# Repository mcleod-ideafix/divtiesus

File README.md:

# DivTIESUS
DivTIESUS is a SD/MMC card interface for the ZX Spectrum. First designed by Mario Pratto as DivMMC, DivTIESUS is an independent design, compatible with the I/O ports and mapper used both in DivIDE and DivMMC, but adding more features.

There is a larger version of DivTIESUS, nicknamed "Pijus Magnificus" edition. This one is the "Tiesus del tó" version, which I have released for the community, so anyone can build his/her own interface.

# Features
- DivMMC compatible interface with 8 KiB of EEPROM and 128 KiB of RAM. Standard utils for EEPROM flashing, as provided by the ESXDOS team, are compatible with DivTIESUS.
- Model autodetection. This means you don't need to put a jumper, or flip a switch to change from using it with a Spectrum 48K and a +3.
- Tested with ZX Spectrum 48K issue 1, 2, 3, 3B, 4A, 4B and 6A. NEC and Hitachi ROM chips. Also tested on Inves Spectrum, Spectrum 128K (both english and spanish versions), +2 grey, +2A, +2B and +3. Also tested on Harlequin 48K. Compatible with TK90X also.
- It uses its own fast clock (25 MHz). It does not need the CPU clock at all.
- Rear expansion port continuation, allowing the user to plug another device. Note that ROMCS and other signals are not filtered.
- NMI button to call file browser in ESXDOS, and handy RESET button. The RESET button is placed so that it won't be accidentally pressed while operating the interface.
- Standard SD card slot (accepts both big SD cards and microSD cards (with adapter).
- A single switch is used to indicate DivTIESUS that the EEPROM can be flashed (JP2 equivalent) and the automapping feature is disabled.
- Visual feedback for SD activity (blue led) and update EEPROM mode (red led).
- ESXDOS shadowing does not collide with all-RAM feature in +2A/B/3 machines. If the system is in all-RAM mode, ESXDOS ROM mapping is disabled.
- Soft +3E feature: DivTIESUS is able to load +3E ROM images from the SD card, install them as the system ROM (using its own RAM), and make them available to the computer, while disabling the automapping feature (needed for ESXDOS but not for +3eDOS). This, effectively, allows the user to operate his/her +2A/B/3 machine as a +2e/3e one, all without having to open the case and exchange ROMs. A new dot command, ".go3e" makes this possible. Such command only works with DivTIESUS.
- Soft ROM feature: the soft +3E feature can also be used to load any 16K, 32K or 64K ROM and make the computer to boot with that ROM (the dot command currently supports only 16K ROMs). This means that ROM images for some util/games available for the Spectrum can be run in their original form. No need to have a +2A/B/3 machine to use them.

# Pictures

# Schematic, board and layout (top and flipped bottom side)

# Build
- First, you need the DivTIESUS PCB. You can order it from JLCPCB using the files in "gerber" directory. They are already tailored for JLCPCB PCB process.
- Second: get the component list. Following is the BOM, with Mouser references to get parts from them, but most of the components are rather standard so you can get it from severla other distributors. Many of them can also be obtained from Aliexpress.

## Bill of materials
|Qty|Value|PCB part|Mouser ref.|
| ------------ | ------------ | ------------ | ------------ |
|2|WS-TATU-TH 431256058726|NMI, RESET|710-431256058726|
|1|SDCARD SLOT|SDCARD|523-GMC020080HR|
|2|1K|R1, R5|603-RC0603FR-131KL|
|5|10K|R2, R4, R6, R7, R8|603-RC0603FR-1310KL|
|3|10uF|C1, C2, C13|581-0805YC106KAT2A|
|1|22K|R3|603-RC0603FR-1322KL|
|1|25 MHz 3225|Q1|520-3225Q-33-240-BST|
|1|28C64ASO|IC2|556-AT28C64B15SU|
|10|100nF|C3, C4, C5, C6, C7, C8, C9, C10, C11, C12|581-0603YC104J4T4A|
|1|CONECTOR_BUS_TRASERO|U$1|571-5530843-6|
|1|EPM240T100C4|IC3|989-EPM240T100C4|
|1|IS65C1024ALSO32|IC4|727-CY62128ELL45SXIT|
|1|JTAG|JTAG|517-N2510-6002RB|
|1|LED0805-BLUE|SD ACTIVITY|710-150080BS75000|
|1|LED0805-RED|FIRMWARE UPDATE ENABLED|710-150080RS75000|
|1|LM1117-3.3|IC1|511-LD1117S33|
|1|SWITCH_SMD_6PIN|JUMPER_E|4000030382277 (Aliexpress)|

- The oscillator does not need to be 25 MHz. It can be about any value between 14 and 30 MHz (it may even work with values outside these limits -not tested-)
- It is very advisable to use a stencil and solder paste for the soldering process. You don't really need a reflow oven, as parts can be soldered using hot air. There are plenty of Youtube videos covering the matter.
- Start placing passives (resistors, capacitors, going from right to left. Leave the SRAM, EEPROM, SD socket and CPLD for the end (in this order). Don't place thru-hole components yet.
- Reflow the top side using an oven, hot plate or hot air. For two pad parts you can even apply the solder tip a few seconds on each pad to allow reflowing it, while keeping the part in place with a pair of tweezers. Same method can be used with SOT-223 parts (the 3.3V regulator), the SD card slot and the SMD switch.
- Turn the board and put-place-solder the two leds. Be aware of polarity with them. Also be aware that these components are very delicate and won't hold much heat, so try to not to apply too much heat and for too much time. You can see in the PCB that (K)athode and (A)node are marked. If you don't like red and blue, use whichever colours you like (or have available).

## First electrical testing
- Check that there is no shortcircuits at the 5V and 3.3V power rails.
- Check that there is no shorts between adjacent pads at the CPLD chip. You may need a magnifying glass to do that. Shorts between adjacent pins at the SRAM or CPLD are easier to notice (I hope).
- To fix any shorts, paste flux is your very best friend. Use it wisely. To me, AMTECH NC-559 solder flux is the best thing to have around (be aware of imitations in Aliexpress!)

After all this first checks, proceed to build and solder the ZX Spectrum bus connector:

## ZX Spectrum bus connector
- Take the 2x28 pin edge connector and cut about 1-2mm on each side to leave the ends opened, as in the last picture of this section.
- With a pair of tweezers, pull and extract the two metal contacts that are positioned at 5th place, where the index tab will be.

- Now take a small piece you can get from a PCB, 1.5mm thick and 7mm tall. This will be the index tab.

- Place the piece in the index hole. Sand it if it's too tall for the hole.

- Using a pair of pliers, push it in place. If it's too small for the hole, use some glue to keep it from coming loose.

Now the edge connector is ready to work as a ZX Spectrum rear bus connector!                                                      

# FAQ (in progress)
***Is this the same version as you have already on sale?***
Almost! This version is the basic version, which is also the cheapest one I've made. Although it's the "basic" version, it has plenty of features, not present in any other DivMMC-like interface, atm.

***Can I take this, build or have someone else build some units, sell them and make some profit?***
I'm ok with that. I only ask you two things: do not remove my copyright noptice from the silk screen and any other document present in this repository, and if you make changes, additions, or otherwise improve the board, make those changes public and available for others as well.

***Can I adapt the Verilog code for a Xilinx part, like XC95144XL?***
Yes, but take into account that XC95 CPLDs doesn't have programmmable pull-ups, so you might need to add some 10K resistors to the board.

***Can I use 512K SRAM chips instead of 128K? Will the board recognize and use it at full capacity?***
Yes to both questions.

***I can see a "divmmc_mcleod_nom1.v" file with a version of the DivMMC module that isn't being used. What is that for?***
Glad you asked! It's an experimental DivMMC module that **DOESN'T NEED THE M1 SIGNAL FROM THE Z80**. It's experimental in the way that it works most of the time, but sometimes, not. If you program the CPLD with this version, it will use the RFSH signal instead of M1 to map and unmap the EEPROM, and a slighly sofisticated method to find out if it is in a M1 cycle, or memory read cycle, to inmediately map the EEPROM for TRDOS traps. More on this later.

***What "tiesus-del-tó" means?***
It means "really really broke".

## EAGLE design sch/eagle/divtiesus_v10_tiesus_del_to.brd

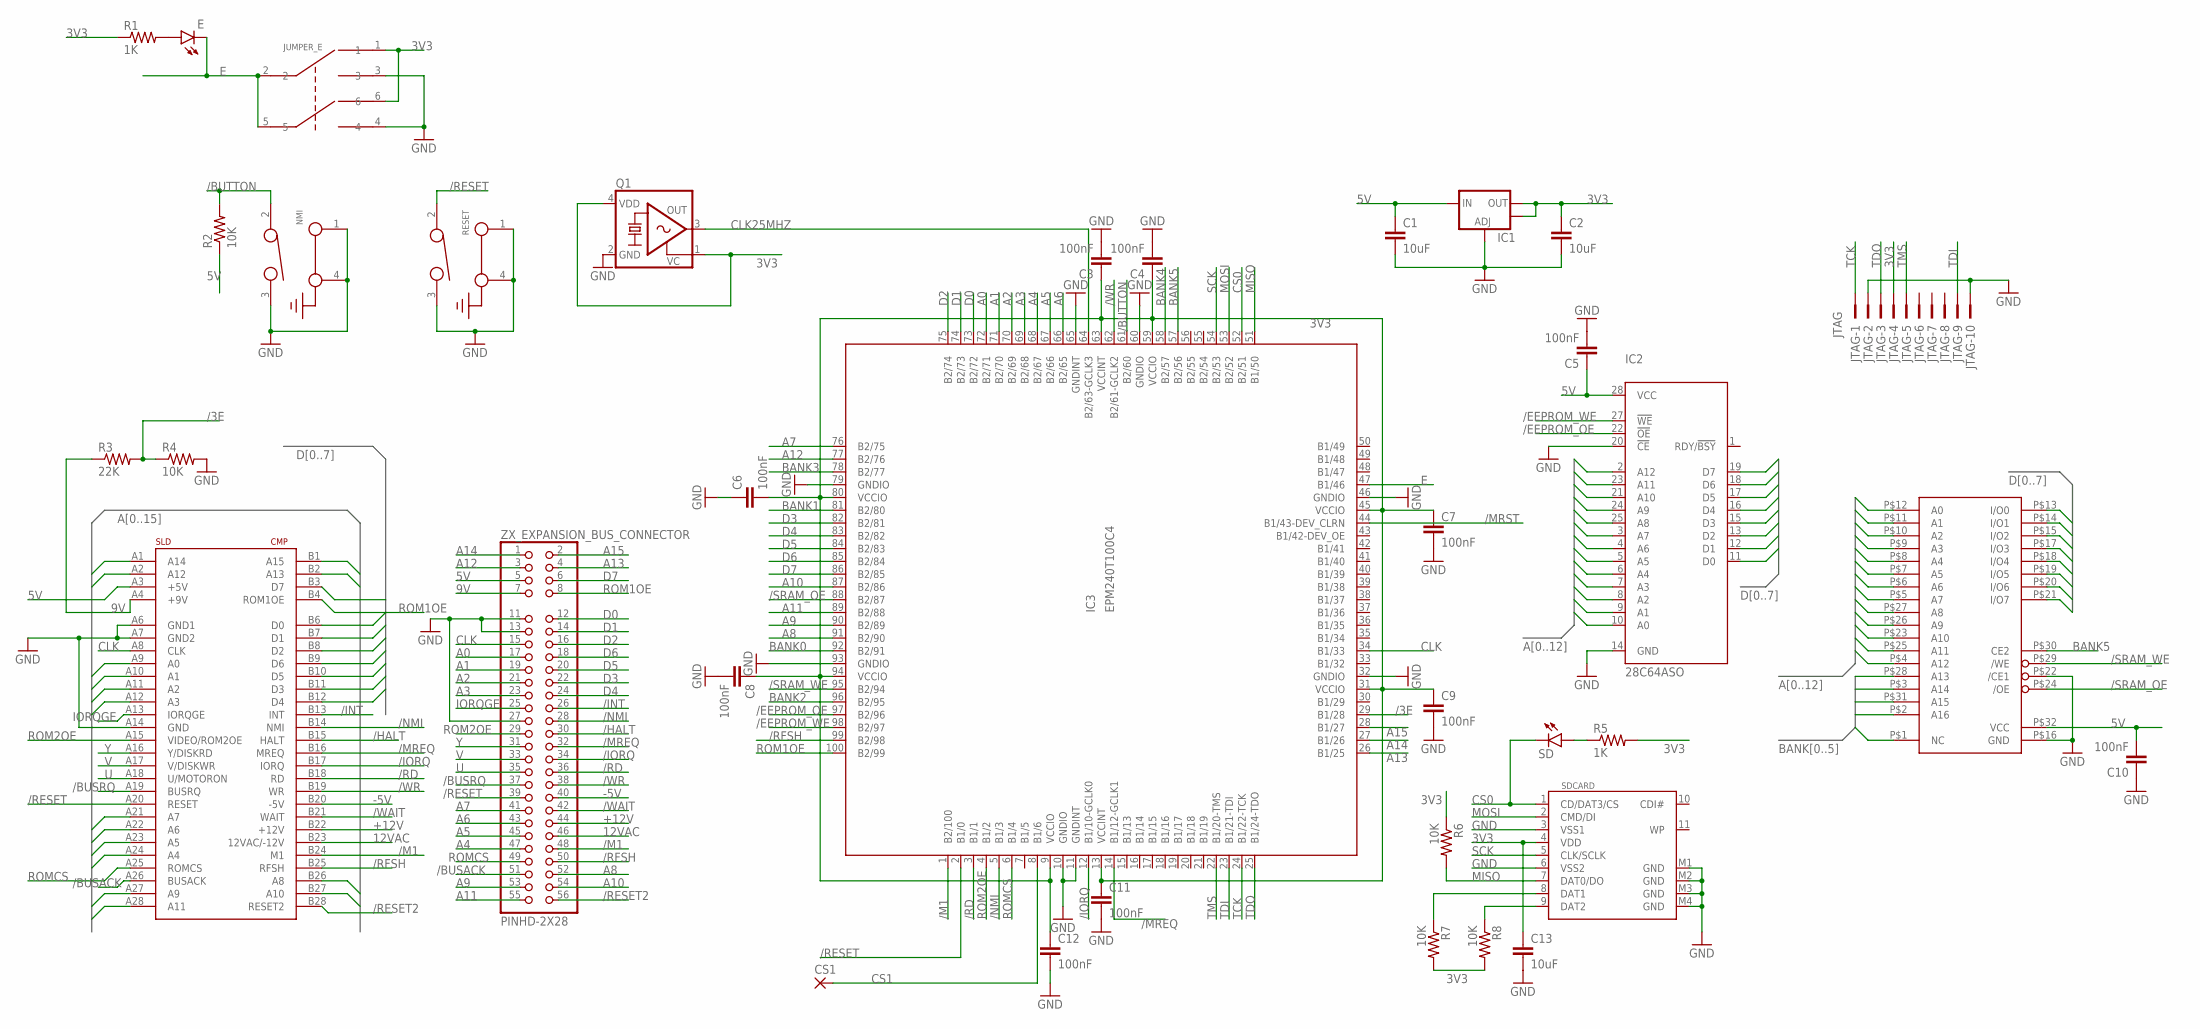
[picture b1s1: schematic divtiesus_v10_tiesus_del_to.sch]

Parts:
C1, C2, C13: 10uF; C0805
C3, C4, C5, C6, C7, C8, C9, C10, C11, C12: 100nF; C0603K
CS1: SMD2; SMD1,27-2,54
E: LEDCHIPLED_0805; CHIPLED_0805
IC1: V_REG_LM1117SOT223; SOT223
IC2: 28C64ASO; SO28W
IC3: EPM240T100C4; TQFP100
IC4: IS65C1024ALSO32; SO32-545MIL
JTAG: JTAG; PAK100/2500-10
JUMPER_E: SWITCH_SMD_6PIN; SMD-6PIN
NMI: 431256083716
Q1: KXO-VCTCXO-SINE-84; 3.2X2.5_KXO-84-VCTCXO
R1, R5: 1K; R0603
R2, R4, R6, R7, R8: 10K; R0603
R3: 22K; R0603
RESET: 431256083716
SD: LEDCHIPLED_0805; CHIPLED_0805
SDCARD: SDCARD; SDCMF-10915W010
U$1: CONECTOR_BUS_TRASERO; CONECTOR_SIMPLE_CARA
ZX_EXPANSION_BUS_CONNECTOR: PINHD-2X28; 2X28

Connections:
3V3: C2.1, C3.1, C4.1, C6.2, C7.1, C8.1, C9.1, C11.1, C12.1, C13.1, IC1.2 (OUT), IC1.4 (OUT), IC3.9 (VCCIO), IC3.13 (VCCINT), IC3.31 (VCCIO), IC3.45 (VCCIO), IC3.59 (VCCIO), IC3.63 (VCCINT), IC3.80 (VCCIO), IC3.94 (VCCIO), JTAG.4, JUMPER_E.1, JUMPER_E.6, Q1.1 (VC), Q1.4 (VDD), R1.1, R5.2, R6.1, R7.2, R8.2, SDCARD.4 (VDD)
5V: C1.1, C5.1, C10.2, IC1.3 (IN), IC2.28 (VCC), IC4.P$32 (VCC), R2.1, U$1.A3 (+5V), ZX_EXPANSION_BUS_CONNECTOR.5
9V: R3.1, U$1.A4 (+9V), ZX_EXPANSION_BUS_CONNECTOR.7
12VAC: U$1.B23 (12VAC/-12V), ZX_EXPANSION_BUS_CONNECTOR.46
+12V: U$1.B22 (+12V), ZX_EXPANSION_BUS_CONNECTOR.44
-5V: U$1.B20 (-5V), ZX_EXPANSION_BUS_CONNECTOR.40
/3E: IC3.29 (B1/28), R3.2, R4.1
/BUSACK: U$1.A26 (BUSACK), ZX_EXPANSION_BUS_CONNECTOR.51
/BUSRQ: U$1.A19 (BUSRQ), ZX_EXPANSION_BUS_CONNECTOR.37
/BUTTON: IC3.61 (B2/60), NMI.2, R2.2
/EEPROM_OE: IC2.22 (!OE), IC3.97 (B2/96)
/EEPROM_WE: IC2.27 (!WE), IC3.98 (B2/97)
/HALT: U$1.B15 (HALT), ZX_EXPANSION_BUS_CONNECTOR.30
/INT: U$1.B13 (INT), ZX_EXPANSION_BUS_CONNECTOR.26
/IORQ: IC3.12 (B1/10-GCLK0), U$1.B17 (IORQ), ZX_EXPANSION_BUS_CONNECTOR.34
/M1: IC3.1 (B2/100), U$1.B24 (M1), ZX_EXPANSION_BUS_CONNECTOR.48
/MREQ: IC3.14 (B1/12-GCLK1), U$1.B16 (MREQ), ZX_EXPANSION_BUS_CONNECTOR.32
/MRST: IC3.44 (B1/43-DEV_CLRN)
/NMI: IC3.5 (B1/3), U$1.B14 (NMI), ZX_EXPANSION_BUS_CONNECTOR.28
/RD: IC3.3 (B1/1), U$1.B18 (RD), ZX_EXPANSION_BUS_CONNECTOR.36
/RESET: IC3.2 (B1/0), RESET.2, U$1.A20 (RESET), ZX_EXPANSION_BUS_CONNECTOR.39
/RESET2: U$1.B28 (RESET2), ZX_EXPANSION_BUS_CONNECTOR.56
/RFSH: IC3.99 (B2/98), U$1.B25 (RFSH), ZX_EXPANSION_BUS_CONNECTOR.50
/SRAM_OE: IC3.88 (B2/87), IC4.P$24 (/OE)
/SRAM_WE: IC3.95 (B2/94), IC4.P$29 (/WE)
/WAIT: U$1.B21 (WAIT), ZX_EXPANSION_BUS_CONNECTOR.42
/WR: IC3.62 (B2/61-GCLK2), U$1.B19 (WR), ZX_EXPANSION_BUS_CONNECTOR.38
A0: IC2.10 (A0), IC3.72 (B2/71), IC4.P$12 (A0), U$1.A9 (A0), ZX_EXPANSION_BUS_CONNECTOR.17
A1: IC2.9 (A1), IC3.71 (B2/70), IC4.P$11 (A1), U$1.A10 (A1), ZX_EXPANSION_BUS_CONNECTOR.19
A2: IC2.8 (A2), IC3.70 (B2/69), IC4.P$10 (A2), U$1.A11 (A2), ZX_EXPANSION_BUS_CONNECTOR.21
A3: IC2.7 (A3), IC3.69 (B2/68), IC4.P$9 (A3), U$1.A12 (A3), ZX_EXPANSION_BUS_CONNECTOR.23
A4: IC2.6 (A4), IC3.68 (B2/67), IC4.P$8 (A4), U$1.A24 (A4), ZX_EXPANSION_BUS_CONNECTOR.47
A5: IC2.5 (A5), IC3.67 (B2/66), IC4.P$7 (A5), U$1.A23 (A5), ZX_EXPANSION_BUS_CONNECTOR.45
A6: IC2.4 (A6), IC3.66 (B2/65), IC4.P$6 (A6), U$1.A22 (A6), ZX_EXPANSION_BUS_CONNECTOR.43
A7: IC2.3 (A7), IC3.76 (B2/75), IC4.P$5 (A7), U$1.A21 (A7), ZX_EXPANSION_BUS_CONNECTOR.41
A8: IC2.25 (A8), IC3.91 (B2/90), IC4.P$27 (A8), U$1.B26 (A8), ZX_EXPANSION_BUS_CONNECTOR.52
A9: IC2.24 (A9), IC3.90 (B2/89), IC4.P$26 (A9), U$1.A27 (A9), ZX_EXPANSION_BUS_CONNECTOR.53
A10: IC2.21 (A10), IC3.87 (B2/86), IC4.P$23 (A10), U$1.B27 (A10), ZX_EXPANSION_BUS_CONNECTOR.54
A11: IC2.23 (A11), IC3.89 (B2/88), IC4.P$25 (A11), U$1.A28 (A11), ZX_EXPANSION_BUS_CONNECTOR.55
A12: IC2.2 (A12), IC3.77 (B2/76), IC4.P$4 (A12), U$1.A2 (A12), ZX_EXPANSION_BUS_CONNECTOR.3
A13: IC3.26 (B1/25), U$1.B2 (A13), ZX_EXPANSION_BUS_CONNECTOR.4
A14: IC3.27 (B1/26), U$1.A1 (A14), ZX_EXPANSION_BUS_CONNECTOR.1
A15: IC3.28 (B1/27), U$1.B1 (A15), ZX_EXPANSION_BUS_CONNECTOR.2
BANK0: IC3.92 (B2/91), IC4.P$28 (A13)
BANK1: IC3.81 (B2/80), IC4.P$3 (A14)
BANK2: IC3.96 (B2/95), IC4.P$31 (A15)
BANK3: IC3.78 (B2/77), IC4.P$2 (A16)
BANK4: IC3.58 (B2/57), IC4.P$1 (NC)
BANK5: IC3.57 (B2/56), IC4.P$30 (CE2)
CLK: IC3.34 (B1/33), U$1.A8 (CLK), ZX_EXPANSION_BUS_CONNECTOR.15
CLK25MHZ: IC3.64 (B2/63-GCLK3), Q1.3 (OUT)
CS0: IC3.52 (B2/51), SD.C, SDCARD.1 (CD/DAT3/CS)
CS1: CS1.1, IC3.8 (B1/6)
D0: IC2.11 (D0), IC3.73 (B2/72), IC4.P$13 (I/O0), U$1.B6 (D0), ZX_EXPANSION_BUS_CONNECTOR.12
D1: IC2.12 (D1), IC3.74 (B2/73), IC4.P$14 (I/O1), U$1.B7 (D1), ZX_EXPANSION_BUS_CONNECTOR.14
D2: IC2.13 (D2), IC3.75 (B2/74), IC4.P$15 (I/O2), U$1.B8 (D2), ZX_EXPANSION_BUS_CONNECTOR.16
D3: IC2.15 (D3), IC3.82 (B2/81), IC4.P$17 (I/O3), U$1.B11 (D3), ZX_EXPANSION_BUS_CONNECTOR.22
D4: IC2.16 (D4), IC3.83 (B2/82), IC4.P$18 (I/O4), U$1.B12 (D4), ZX_EXPANSION_BUS_CONNECTOR.24
D5: IC2.17 (D5), IC3.84 (B2/83), IC4.P$19 (I/O5), U$1.B10 (D5), ZX_EXPANSION_BUS_CONNECTOR.20
D6: IC2.18 (D6), IC3.85 (B2/84), IC4.P$20 (I/O6), U$1.B9 (D6), ZX_EXPANSION_BUS_CONNECTOR.18
D7: IC2.19 (D7), IC3.86 (B2/85), IC4.P$21 (I/O7), U$1.B3 (D7), ZX_EXPANSION_BUS_CONNECTOR.6
E: E.C, IC3.47 (B1/46), JUMPER_E.2, JUMPER_E.5
GND: C1.2, C2.2, C3.2, C4.2, C5.2, C6.1, C7.2, C8.2, C9.2, C10.1, C11.2, C12.2, C13.2, IC1.1 (ADJ), IC2.14 (GND), IC2.20 (!CE), IC3.10 (GNDIO), IC3.11 (GNDINT), IC3.32 (GNDIO), IC3.46 (GNDIO), IC3.60 (GNDIO), IC3.65 (GNDINT), IC3.79 (GNDIO), IC3.93 (GNDIO), IC4.P$16 (GND), IC4.P$22 (/CE1), JTAG.2, JTAG.10, JUMPER_E.3, JUMPER_E.4, NMI.1 (GND1), NMI.3, NMI.4 (GND), Q1.2 (GND), R4.2, RESET.1 (GND1), RESET.3, RESET.4 (GND), SDCARD.3 (VSS1), SDCARD.6 (VSS2), SDCARD.M1 (GND), SDCARD.M2 (GND), SDCARD.M3 (GND), SDCARD.M4 (GND), U$1.A6 (GND1), U$1.A7 (GND2), U$1.A14 (GND), ZX_EXPANSION_BUS_CONNECTOR.11, ZX_EXPANSION_BUS_CONNECTOR.13, ZX_EXPANSION_BUS_CONNECTOR.27
IORQGE: U$1.A13 (IORQGE), ZX_EXPANSION_BUS_CONNECTOR.25
MISO: IC3.51 (B1/50), R6.2, SDCARD.7 (DAT0/DO)
MOSI: IC3.53 (B2/52), SDCARD.2 (CMD/DI)
unnamed: R5.1, SD.A
unnamed: E.A, R1.2
unnamed: R7.1, SDCARD.8 (DAT1)
unnamed: R8.1, SDCARD.9 (DAT2)
ROM1OE: IC3.100 (B2/99), U$1.B4 (ROM1OE), ZX_EXPANSION_BUS_CONNECTOR.8
ROM2OE: IC3.4 (B1/2), U$1.A15 (VIDEO/ROM2OE), ZX_EXPANSION_BUS_CONNECTOR.29
ROMCS: IC3.6 (B1/4), U$1.A25 (ROMCS), ZX_EXPANSION_BUS_CONNECTOR.49
SCK: IC3.54 (B2/53), SDCARD.5 (CLK/SCLK)
TCK: IC3.24 (B1/22-TCK), JTAG.1
TDI: IC3.23 (B1/21-TDI), JTAG.9
TDO: IC3.25 (B1/24-TDO), JTAG.3
TMS: IC3.22 (B1/20-TMS), JTAG.5
U: U$1.A18 (U/MOTORON), ZX_EXPANSION_BUS_CONNECTOR.35
V: U$1.A17 (V/DISKWR), ZX_EXPANSION_BUS_CONNECTOR.33
Y: U$1.A16 (Y/DISKRD), ZX_EXPANSION_BUS_CONNECTOR.31

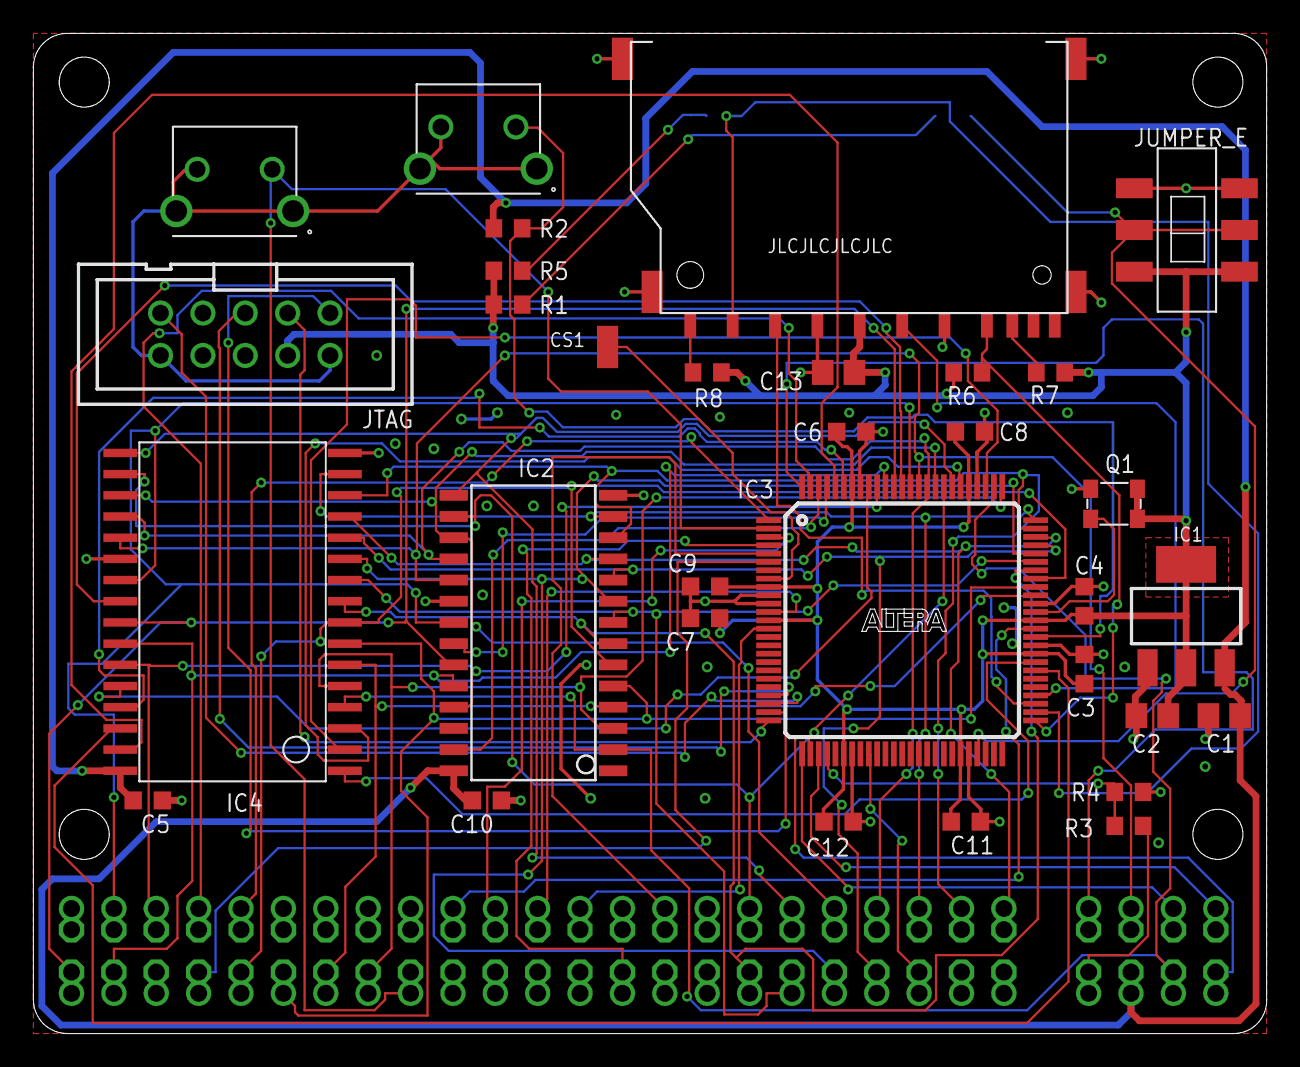
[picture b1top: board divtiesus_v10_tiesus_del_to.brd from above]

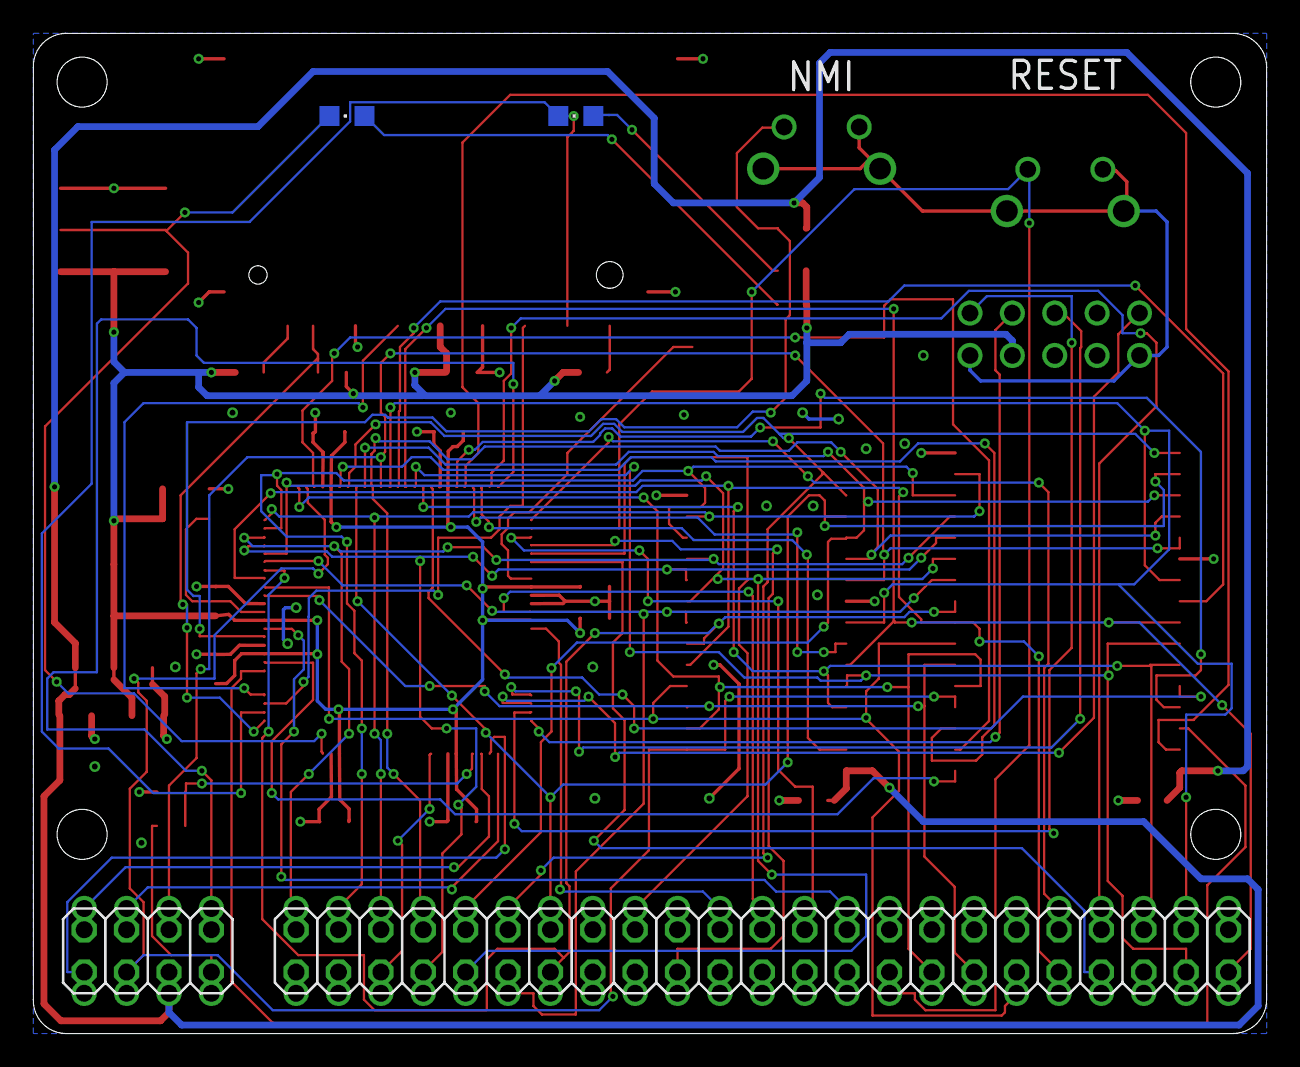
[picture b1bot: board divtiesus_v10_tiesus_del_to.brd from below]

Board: 2 copper layers, 73.9 x 59.9 mm, 36 parts (4 on the bottom side), 80 nets.

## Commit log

2023-04-29 Update README.md
    Fixed Mouser reference for LM1117 type regulator.
2024-01-23 Add UART support for connecting WiFi module
    pin 43 is TX, pin 48 is RX, pin 50 is RTS. UART implementation is taken
    from ZX Uno core

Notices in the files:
parts and their libraries:
Eagle_SWITCHES: Copyright: Würth Elektronik
crystal-geyer_V1_0: Copyright: Geyer-Electronic
